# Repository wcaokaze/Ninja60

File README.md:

Ninja60 (WIP)
================================================================================

私の手にフィットするように設計した60%キーボードです

いわゆる左手デバイスとして使うことも想定しているのでロータリーエンコーダを4つ付ける予定です

ビルドガイド
--------------------------------------------------------------------------------

とくにカスタマイズなどしないのであれば[things](things)に出力済みのstlがあります

カスタマイズする場合は[scad](scad)をご覧ください

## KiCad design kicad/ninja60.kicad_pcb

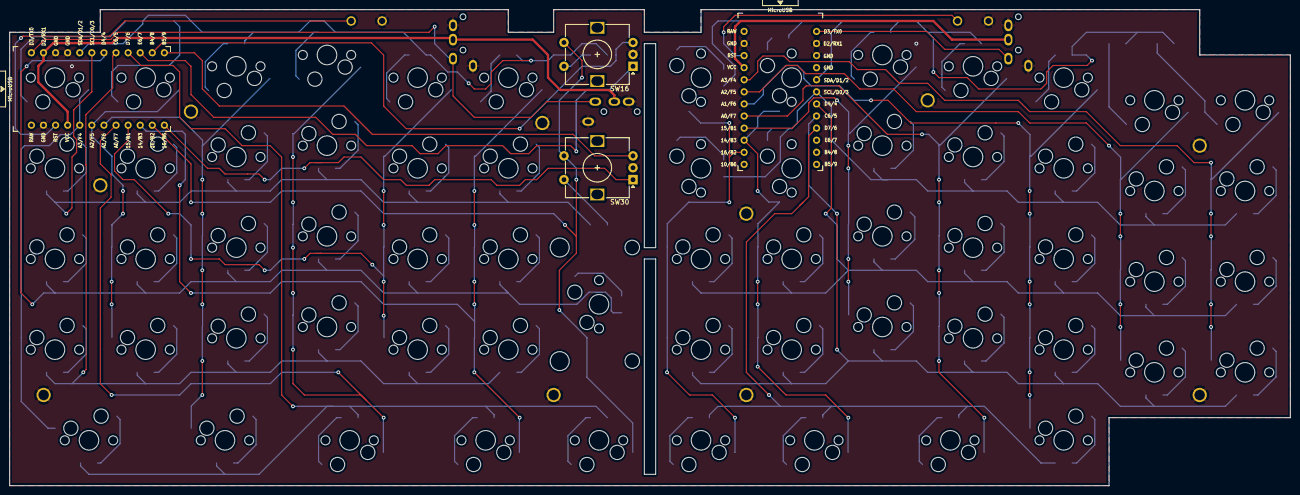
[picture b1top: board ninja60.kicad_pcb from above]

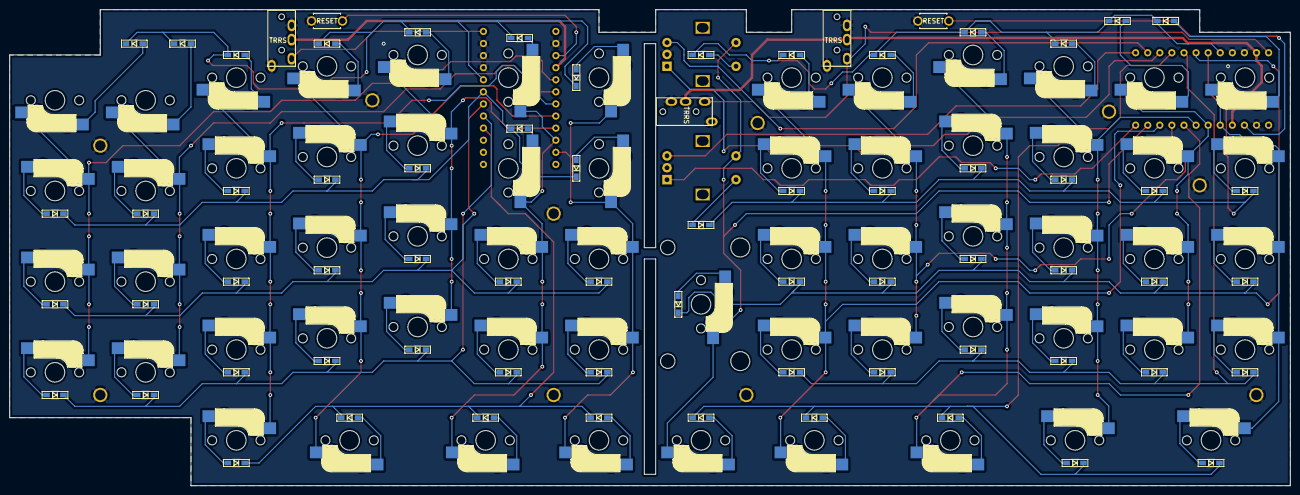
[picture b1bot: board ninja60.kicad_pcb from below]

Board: 2 copper layers, 269.1 x 100.0 mm, 136 parts (69 on the bottom side), 99 nets.

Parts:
D1, D2, D3, D4, D5, D6, D7, D8, D9, D10, D11, D12, D13, D14, D15, D16, D17, D18, D19, D20, D21, D22, D23, D24, D25, D26, D27, D28, D29, D30, D31, D32, D33, D34, D35, D36, D37, D38, D39, D40, D41, D42, D43, D44, D45, D46, D47, D48, D49, D50, D51, D52, D53, D54, D55, D56, D57, D58, D59, D60, D61, D62, D63, D64: D; D3_SMD_v2
J1, J2, J3: MJ-4PP-9; MJ-4PP-9_1side
Ref**: Val**; CherryMX_MidHeight_Choc_Hotswap_2U_Outline
SW1, SW2: SW_PUSH; ResetSW_1side
SW3, SW4, SW5, SW6, SW7, SW8, SW9, SW10, SW11, SW12, SW13, SW14, SW15, SW17, SW18, SW19, SW20, SW21, SW22, SW23, SW24, SW25, SW26, SW27, SW28, SW29, SW31, SW32, SW33, SW34, SW35, SW36, SW37, SW38, SW39, SW40, SW41, SW42, SW43, SW44, SW45, SW46, SW47, SW48, SW49, SW50, SW51, SW52, SW53, SW54, SW55, SW56, SW57, SW58, SW59, SW62, SW63, SW66: SW_PUSH; CherryMX_Hotswap
SW16, SW30: Rotary_Encoder_Switch; RotaryEncoder_Alps_EC12E-Switch_Vertical_H20mm
SW60, SW61, SW64, SW65: SW_PUSH; CherryMX_Hotswap_1.5u
U1, U2: ProMicro; ProMicro_v3.5

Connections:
GND: J1.A, J1.B, J2.A, J2.B, J3.A, J3.B, SW1.2, SW2.2, SW16.C, SW30.C, U1.3, U1.4, U1.23, U2.2, U2.3, U2.4, U2.23
unnamed: D1.2, SW3.2
unnamed: D2.2, SW4.2
unnamed: D3.2, SW5.2
unnamed: D4.2, SW6.2
unnamed: D5.2, SW7.2
unnamed: D6.2, SW8.2
unnamed: D7.2, SW9.2
unnamed: D8.2, SW10.2
unnamed: D9.2, SW11.2
unnamed: D10.2, SW12.2
unnamed: D11.2, SW13.2
unnamed: D12.2, SW14.2
unnamed: D13.2, SW15.2
unnamed: D14.2, SW16.S1
unnamed: D15.2, SW17.2
unnamed: D16.2, SW18.2
unnamed: D17.2, SW19.2
unnamed: D18.2, SW20.2
unnamed: D19.2, SW21.2
unnamed: D20.2, SW22.2
unnamed: D21.2, SW23.2
unnamed: D22.2, SW24.2
unnamed: D23.2, SW25.2
unnamed: D24.2, SW26.2
unnamed: D25.2, SW27.2
unnamed: D26.2, SW28.2
unnamed: D27.2, SW29.2
unnamed: D28.2, SW30.S1
unnamed: D29.2, SW31.2
unnamed: D30.2, SW32.2
unnamed: D31.2, SW33.2
unnamed: D32.2, SW34.2
unnamed: D33.2, SW35.2
unnamed: D34.2, SW36.2
unnamed: D35.2, SW37.2
unnamed: D36.2, SW38.2
unnamed: D37.2, SW39.2
unnamed: D38.2, SW40.2
unnamed: D39.2, SW41.2
unnamed: D40.2, SW42.2
unnamed: D41.2, SW43.2
unnamed: D42.2, SW44.2
unnamed: D43.2, SW45.2
unnamed: D44.2, SW46.2
unnamed: D45.2, SW47.2
unnamed: D46.2, SW48.2
unnamed: D47.2, SW49.2
unnamed: D48.2, SW50.2
unnamed: D49.2, SW51.2
unnamed: D50.2, SW52.2
unnamed: D51.2, SW53.2
unnamed: D52.2, SW54.2
unnamed: D53.2, SW55.2
unnamed: D54.2, SW56.2
unnamed: D55.2, SW57.2
unnamed: D56.2, SW58.2
unnamed: D57.2, SW59.2
unnamed: D58.2, SW60.2
unnamed: D59.2, SW61.2
unnamed: D60.2, SW62.2
unnamed: D61.2, SW63.2
unnamed: D62.2, SW64.2
unnamed: D63.2, SW65.2
unnamed: D64.2, SW66.2
VCC: J1.C, J3.C, U1.2, U1.21
encoder0_a: SW16.A, U1.10
encoder0_b: SW16.B, U1.11
encoder1_a: SW30.A, U1.13
encoder1_b: SW30.B, U1.12
l_col0: SW3.1, SW17.1, SW31.1, SW45.1, SW58.1, U1.20
l_col1: SW4.1, SW18.1, SW32.1, SW46.1, U1.19
l_col2: SW5.1, SW19.1, SW33.1, SW47.1, SW59.1, U1.18
l_col3: SW6.1, SW20.1, SW34.1, SW48.1, SW60.1, U1.17
l_col4: SW7.1, SW21.1, SW35.1, SW49.1, U1.16
l_col5: SW8.1, SW22.1, SW36.1, SW50.1, SW61.1, U1.15
l_col6: SW16.S2, SW30.S2, SW37.1, SW62.1, U1.14
l_data: J1.D, J3.D, U1.1
l_reset: SW1.1, U1.22
l_row0: D1.1, D2.1, D3.1, D4.1, D5.1, D6.1, D14.1, U1.5
l_row1: D15.1, D16.1, D17.1, D18.1, D19.1, D20.1, D28.1, U1.6
l_row2: D29.1, D30.1, D31.1, D32.1, D33.1, D34.1, D35.1, U1.7
l_row3: D43.1, D44.1, D45.1, D46.1, D47.1, D48.1, U1.8
l_row4: D56.1, D57.1, D58.1, D59.1, D60.1, U1.9
r_VCC: J2.C, U2.21
r_col0: SW15.1, SW29.1, SW44.1, SW57.1, U2.20
r_col1: SW14.1, SW28.1, SW43.1, SW56.1, U2.19
r_col2: SW13.1, SW27.1, SW42.1, SW55.1, SW66.1, U2.18
r_col3: SW12.1, SW26.1, SW41.1, SW54.1, SW65.1, U2.17
r_col4: SW11.1, SW25.1, SW40.1, SW53.1, U2.16
r_col5: SW10.1, SW24.1, SW39.1, SW52.1, SW64.1, U2.15
r_col6: SW9.1, SW23.1, SW38.1, SW51.1, SW63.1, U2.14
r_data: J2.D, U2.1
r_reset: SW2.1, U2.22
r_row0: D7.1, D8.1, D9.1, D10.1, D11.1, D12.1, D13.1, U2.5
r_row1: D21.1, D22.1, D23.1, D24.1, D25.1, D26.1, D27.1, U2.6
r_row2: D36.1, D37.1, D38.1, D39.1, D40.1, D41.1, D42.1, U2.7
r_row3: D49.1, D50.1, D51.1, D52.1, D53.1, D54.1, D55.1, U2.8
r_row4: D61.1, D62.1, D63.1, D64.1, U2.9

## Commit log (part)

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2020-11-13 試作2号のデータをコピー
2020-12-17 とりあえず台形のみ作成
2020-12-17 角を丸くした
2020-12-18 テント/チルト型にしてみた
2020-12-18 四角錐といいますか、上の方が狭い形にしてみました
2020-12-18 ステム部を作りました
2020-12-18 ステムの周りに柱を立てます
2020-12-18 ステム周りにさらに円柱立てていく
2020-12-18 向きがわかるようにわずかに柱の高さを変えた
2020-12-18 1U以外のサイズのキーキャップも作れるようにしました。1.75Uしか使わないですけどね
2020-12-19 シリンドリカルのキーも多少斜めっているかのように見えるようにした
2020-12-19 縦長のキーも作れるようにした
2020-12-19 ステムの周りの柱を0.5mm下げた
2020-12-19 ステム以外を全体的に上に上げた
2020-12-20 ステムが一番奥まで入らない説があったのでさらに1mm高くしました
2020-12-20 ホームポジションのマークをつけた
    ホームポジションのマークってなんか名前あった気がするけど思い出せないのでhome_position_markにしてます
2020-12-20 ホームポジションマークの位置と大きさを調整
2020-12-20 背の高いfnキーを7列目に移動
2020-12-20 右手側が山の形になるように並び替え
2020-12-20 キー同士の距離が1mmもない状態だったので広くしました
2020-12-20 左手側最下段のキーを右手側最下段と重なる位置に移動
2020-12-21 あと2キー出力できる空間がありそうなので左手7列目を2つ追加
2020-12-22 キーが多すぎてレンダリングできなかったので半分だけ出力します
2020-12-22 上二段を下二段の上に重ねます
2020-12-22 7列目縦長キーの上にホームポジションキーを重ねます
2020-12-22 残りのキーをうまく重ねます
2020-12-23 キーキャップmoduleを別ファイルに移動
2020-12-25 すべてのキーをバラバラに出力してから統合する手法に移行
2020-12-25 ボトムプレートのソケットとかダイオード用の穴をまず作ります
2020-12-26 試しに4キー分だけ作ってみた
2020-12-26 穴開ける用のキースイッチの形状を作成
2020-12-26 トッププレート4キー分作成
2020-12-27 予め回転、移動させた状態でstlを出力するようにした
2020-12-30 refactored: moduleの定義順変更
2020-12-30 ステム部、outerではなくinnerでくり抜くように変更
2020-12-30 ステム部などの円柱を16角柱で代用
2020-12-30 行方向の丸みを強くした
2021-01-03 一旦調整するのでキーキャップ2個だけ並べます
2021-01-03 変数達を先に宣言した方が見やすいきがしました
2021-01-03 中の空洞やっぱり球状に戻します 分厚すぎなので
2021-01-03 ステム部の高さが全然足りてないししかも中心からズレていたのを修正
2021-01-03 ステム部が別になったので他の部分をすべてステム部の高さ分下げます
2021-01-03 柱さらに0.5mm低くします
2021-01-03 クソ縦長キーキャップをやめたことによりもう少し各キー同士の間隔を詰められるようになったので詰めます
2021-01-03 柱の形状を再調整
2021-01-04 ステム部とキーキャップをジョイントするための十字を作成
2021-01-04 高さ足りてなかったのでちゃんと低い方の端の高さを計算するようにしました
2021-01-04 y = [0, 1] => [0.5, 1.5]
2021-01-04 長いキーに傾きをつけました
2021-01-04 refactored: keycap_with_stem追加
2021-01-04 壁があるときは柱を壁まで延ばすようにしました
2021-01-05 キーキャップの外形を刷新、南から北に向かって高くなっていく形状にした
2021-01-05 added: part_cylinder
2021-01-05 そんなことしなくても一時的に$faを変える方法があったらしい もっと早く教えろ
2021-01-06 x < -3 のときの柱を十字に変更
2021-01-06 ケースの曲面用のfaを分けます
2021-01-06 曲面を再度調整
2021-01-06 キーキャップ間の隙間を詰めました
2021-01-06 柱を繰り抜く際outerではなくinnerを使用 わずかに処理が速いので
2021-01-06 いつまでwalls残してんねんコイツ
2021-01-06 本番用visible_faをコメントアウト
2021-01-06 柱を繰り抜く際innerではなくouterを使用するように戻した childrenが反映されなくなってたので
2021-01-06 縦長キーの座標間違えてたので修正
2021-01-07 各moduleにコメントを書いておきました
2021-01-07 renamed: visible_fa => keycap_visible_fa, invisible_fa => keycap_invisible_fa, thickness => keycap_thickness
2021-01-07 renamed: height => keycap_height
2021-01-07 各パーツごとにファイルを分けました
2021-01-07 結合部の寸法の微調整が簡単にできるようにしました
2021-01-07 ステムホルダー タテヨコがパッとわかるようにしたかったので横長にしました
2021-01-07 キーキャップの時と同様に各パーツごとに$faをべつべつに指定
2021-01-08 親指のキーたちを円弧状に配置する試み
    結局こうなる
    先人たちに逆らおうとしたってそうはいかない
2021-01-09 各列1°ずつ開いて並べることにします
2021-01-10 角度、座標など微妙にズレがあったので修正
2021-01-10 refactored: keycap_marginという変数を定義しました
2021-01-10 y == -1のキーが実際には下から2段目なのでこのズレを考慮した処理に変更
2021-01-10 各列の角度を2.5°に変更
2021-01-10 staggeredによってy = 1.25とかに配置されるキーも上面の角度はy = 1として出力
2021-01-10 南北の凹みを繋げられるようにした
2021-01-11 親指キーの皿部分を作成
2021-01-16 親指キーの空洞を開けた
2021-01-17 親指キーの柱部分作成
2021-01-18 静音リング部を別パーツに分けた
2021-01-24 刻印を追加
2021-02-01 人差し指で押すつもりだった3キーを小指側に移動
2021-02-01 staggered単位をmmに変更
2021-02-01 いつまで最下段キーのコメントアウト残してんねんこんなもんもう絶対使わんやろ
2021-02-01 親指キーの大きさと位置再調整
2021-02-01 小指外側のキーの柱を十字型に変更
2021-02-03 ケースを2Uずらしたときにbottom_zの計算式を2Uずらすの忘れていたので修正
2021-02-03 親指キーに渡す引数を間違えてクソデカステムが生成されていたのを修正
2021-02-06 小指キー一列減らして親指1キー増やした
2021-02-06 ロータリーエンコーダを配置
2021-02-20 親指キーの側面がポリゴンみたいになってたを曲線に修正、皿部分が扇型だったのを普通のキーキャップと同様長方形に変更
2021-02-22 横キーピッチを18mmに変更、縦は16mmのまま
2021-02-23 皿部分の面積がすべてのキーでほぼ同じになるように調整
2021-02-25 SAプロファイルっぽく底面をシャープに、上面は丸くした
2021-02-25 faをより細かく場所ごとに設定できるようにした
    したけどどっちみち全部2になりそうだった
2021-02-26 親指用キーキャップの引数を中心ではなく外側の半径に変更
2021-02-26 ちょっと皿広くした
2021-02-26 小指と人差し指の外側キーまでの距離だけを16mmに変更
2021-03-01 moved: { 試作3号 => _ }/kicad, { 試作3号 => _ }/scad
2021-03-01 moved: { scad => _ }/res/Cica-Regular.ttf
2021-03-20 GradleからOpenSCAD叩かせます
2021-03-21 使いそうなものをscadwriterとして用意しました
2021-03-21 *.scadの生成と*.stlの生成は違うタスクにしないとさ、うまくいかないよね
2021-03-21 ビルド方法のメモを残しておきました
2021-03-21 added: $fs, $fa, $fn
2021-03-21 cylinderの引数名を明示
2021-03-21 linearExtrude => linear_extrude
2021-03-21 added: <Double>..<Double> step <Double> (Iterable<Double>)
2021-03-21 moved: scadwriter.{ _ => foundation }.Point3d
2021-03-21 added: Angle, Size
2021-03-21 SizeとAngleに各種演算子オーバーロードを実装
2021-03-22 moved: *.scad => com/wcaokaze/ninja60/scadgenerator/*.kt
2021-03-26 foostan/kbdをサブモジュールに追加、kicadにシンボルライブラリを通しました
2021-05-18 openscadのインストール用コマンドのメモを多少親切にした
2021-05-29 moved: com.wcaokaze.ninja60.{ scadgenerator => _ }.*, com.wcaokaze.{ ninja60.scadgenerator.scadwriter => _ }.*
2021-06-02 added: Column
2021-06-02 Columnの各KeyPlateのレイヤー位置をずらせるようにした
2021-06-06 keycapThicknessをKeycapのcompanion objectに移動
2021-06-06 renamed: keyswitch.kt => muteForm.kt
2021-06-06 renamed: topPlate => TopPlate
2021-06-06 added: AlphanumericColumns
2021-06-07 見やすくするためレイヤーを一層だけにした
2021-06-07 scad書き出し処理をTopPlate.ktに移動
2021-06-07 deleted: muteForm.kt
    ミュート使うのやめます
2021-06-07 deleted: KeyPlate.U
2021-06-08 4行6列固定になっていたのを可変に変更。無理そうなら戻します
2021-06-10 added: Vector2d, Vector3d
2021-06-10 added: Line2d, Line3d
2021-06-12 added: Point3d.rotate(Line3d, Angle): Point3d
2021-06-14 added: Line3d.translate, rotate, Vector3d.rotate
2021-06-14 deleted: rotateX, rotateY, rotateZ
2021-06-14 added: Plane3d.intersection(Line3d): Point3d
2021-06-16 added: Vector.innerProduct, vectorProduct, angleWith
2021-06-16 KeyPlateの内部構造を点4つから中心、大きさ、向きふたつに変更
2021-06-20 各プレート同士をつなげた
2021-06-25 一旦List<List<Point3d>>生成するのやめていきなりscad書きます
2021-06-27 KeyPlateの端の部分がきっちり垂直に生成されていなかったのを修正
2021-06-28 キースイッチはめる用の穴を開けました
2021-06-29 確認用にlayerDistance = 0mmのAlphanumericColumnsも表示
2021-06-29 1行目がキー半個分深い位置に生成されてしまっていたのを修正
2021-06-29 左右の一番外側の列を内側に近づけた
2021-06-29 『ひねり』を8°くらいまで落とさないとキー同士が干渉しすぎて無理だと思った
2021-06-29 『ひねり』とは別にColumnそのものを回転させるパラメータも追加
2021-07-12 左右の端に壁を作りました
2021-07-12 なんかもうベツモノになりすぎたので試作の写真を削除
    基板も刻印もなくなったので一旦謝辞も削除
    しかし感謝の心はあります
2021-07-27 refactor: added translate(Vector3d, Size)
2021-07-27 added: ThumbPlate
2021-07-31 作業中にlayerDistanceをいじっていた痕跡が残っていたのを修正
2021-07-31 親指キーの長さを変更できるようにした
    とりあえず1.5U
2021-07-31 親指キーの長さを22.4mmに変更
2021-08-04 数字行を垂直にしてたのを通常の向きに変更
    数字行は使用頻度は高くないものの連続して打たれやすいという性質があるため
    垂直に配置しているとすごく打ちづらいんですね
2021-08-04 左右の壁をなくした
2021-08-04 Revert "AlphanumericPlateを各キーごとに板で出力しようとした版の途中"
    This reverts commit ffdb721cf2262750bd326013f6ed69e2614445aa.
2021-08-05 AlphanumericPlateとThumbPlateを移動できるようにした
2021-08-05 deleted: case.kt
2021-08-09 KeyPlateとKeySwitchを別の概念として分けた。キースイッチの位置と向きだけを持つべき、大きさを持つべきでない部分はすべてKeySwitchに置換
2021-08-09 AlphanumericColumnsとAlphanumericPlate、ThumbKeysとThumbPlateを分ける意味がなくなったのでPlate側に統合
2021-08-10 各Columnの上下端を20mm延ばすようにした
    こうしないとColumn同士の境目の壁が垂直に出力されない
2021-08-11 renamed: Column => AlphanumericColumn
2021-08-11 renamed: alphanumericPlate => hullAlphanumericPlate, thumbPlate => hullThumbPlate
2021-08-14 alphanumericの手前部分ケース作成
2021-08-14 パームレスト部分をとりあえずcubeで置いた
2021-08-22 4段目キーの長さを1.5Uに変更
2021-08-28 KeySwitch.LayoutSizeが追加されたことでより正確に計算できるところがありますね
2021-08-29 added: Transformable
2021-08-29 RotaryEncoderMountHoleにTransformableを実装し忘れてたので実装しました
2021-08-29 ThumbPlateにもTransformableを実装し忘れてたので実装しました
2021-08-29 親指の奥のキーの位置が通常より遠くなっていたのを修正
2021-08-30 アルファベットキーの手前の壁 きちんと角度計算するようにした
2021-09-01 後ろの斜面部分がデコボコしててダサかったので平らにしました
2021-09-06 手前側ロータリーエンコーダの取り付け穴を作りました
2021-09-08 無駄な括弧を削除
2021-09-08 locale(Point3d) 追加
2021-09-10 他のモデル達と同じようにCaseもAlphanumericPlateとThumbPlateを保持するようにします
2021-09-10 Case以外一旦出力しないようにしておきます
2021-09-10 STLを追加
2021-09-10 右手側出力するの忘れてました。しました
2021-09-11 かんたんにREADMEを書きました
2021-09-12 added: Gear
2021-09-13 renamed: Gear.PRESSURE_ANGLE => PROFILE_ANGLE
2021-09-13 added: Gear distance Gear
2021-09-13 奥側ロータリーエンコーダのノブを作成
2021-09-13 BackRotaryEncoderKnobと同様にFrontRotaryEncoderKnobも追加
2021-09-15 奥側ロータリーエンコーダにつける歯車を作成
2021-09-20 奥側ロータリーエンコーダに取り付ける歯車を作成
2021-10-31 奥側ロータリーエンコーダ部分のケースを作成
2021-11-05 ノブがハマる部分の穴を作成
2021-11-10 奥側ノブを取り付けるためのシャフトの穴を開けました
2021-11-24 added: LeftOutRotaryEncoderKnob
2021-11-25 LeftOutRotaryEncoderKnob内にInternalGearをいれました
2021-11-25 renamed: DoubelRangeIterator.kt => DoubleRangeIterator.kt
2021-11-27 added: LeftInnerRotaryEncoderKnob
2021-11-27 LeftInnerRotaryEncoderKnobを押し込むための穴をLeftOuterRotaryEncoderKnobに開けました
2021-11-27 手前側ロータリーエンコーダのノブ周りの穴を左側に合わせて狭くしました
2021-11-28 LeftOuterRotaryEncoderKnobの向き、AlphanumericPlateの左端を基準にした
2021-12-02 faの型をAngleに変更
2021-12-02 fsの型をSizeに変更
2021-12-20 後ろ側ロータリーエンコーダのノブにも滑り止めをつけました
2021-12-20 奥側ロータリーエンコーダのノブの滑り止めを1:1凸凹に変更
2021-12-20 added: rotaryEncoderKnobHole
2021-12-21 親指キーの表面を出力
2021-12-29 親指キーの配置再調整
2022-01-06 手前側ロータリーエンコーダのマウント穴の向きを調整
2022-01-11 CaseをTransformableに変更
2022-01-12 Size, AngleなどでtoStringがScadコード生成用のフォーマットになっていたのを修正、ScadPrimitiveValueを追加
2022-01-17 ScadObjectはScadValueを継承するようにした
2022-01-17 deleted: ScadWriter
2022-01-18 deleted: ScadValue.writeScad
2022-01-20 case生成処理をがっつり書き直しました
2022-02-23 中がよく見えるように一旦ケース外側の壁を消しました
2022-02-26 親指キーの配置を変更
    なんどめだナウシカ
    他のキーと干渉しない配置がもはやこれしかない
    あとついでにSize.div(Size): Double追加しました、角度の場合はAngle(length / radius)で
2022-02-26 手前側ロータリーエンコーダの横のキーを追加
2022-03-01 added: place(Transformable) { children... }
2022-03-01 switchHoleとswitchSideHolderをmemoizeできるようにした
2022-03-12 added: Transformable.btLine, lrLine, fbLine
2022-03-12 added: Point distance Point
2022-03-27 added: BevelGear
2022-03-30 奥側ロータリエンコーダの位置を調整
2022-03-30 各種Rangeにおいてstartがendよりデカいときにstepを負値にしないといけなかったのを修正
2022-04-01 BackRotaryEncoderMediationGearの位置決めの計算に「Z座標」を使っており回転した場合に正確に位置が決まらなくなっていたのを修正
2022-04-03 歯車のサイズなど微調整
2022-04-06 PropagatedValue.valueはScadParentObjectじゃなくてScadObjectに定義しとかないとtoScadRepresentation内で使えないということに気づきました
2022-04-08 faをPropagatedValueに変更
2022-04-08 fsをPropagatedValueに変更
2022-04-08 provideValueの子が全く出力できていなかったのを修正
2022-04-08 先程の変更によってTopLevelScadObjectが無駄な{}を生成してたのも修正できるようになったのでついでに修正しときます
2022-04-08 writeScad直下にすべてのPropagatedValueを明示
2022-04-08 deleted: $fn
2022-04-15 alphanumeric手前側壁を作成
2022-04-16 手前の壁、ノブより左側と右側で分けてそれぞれ最適な高さとかにした
2022-04-17 FrontRotaryEncoder関係のコードからマジックナンバーを排除
2022-04-17 扇形のoffsetをきっちり並行に生成するようにした
2022-04-18 FrontRotaryEncoderKey部分のケースを作成
2022-04-19 親指周りの位置とかデカさとか諸々調整
2022-04-20 added: KeySwitch.KEYCAP_SURFACE_HEIGHT
2022-04-20 親指キーのキーピッチをキーの中心で計算してたけど扇形の内側で計算しないとキー同士がぶつかりますよね
2022-04-20 バウムクーヘン型を生成する関数を作った
2022-04-20 switchHoleにて上部に0.5mm余裕に穴を開けてるつもりが開いてなかったのを修正
2022-04-23 全体的に低くしたった
2022-04-23 パームレスト追加
2022-04-24 モジュールちゃんと分けましょうよってことですね
2022-04-24 shared.ktにあった関数とかをそれぞれのファイルに分けた
2022-04-24 Case.kt内にあるSCAD生成関数をパーツごとにファイルに分割
2022-04-24 Case(data class)とscad生成用関数のパッケージを分けた
2022-04-24 各パーツのインスタンス化の方法、companion objectのinvokeだったのをすべてCaseが担当するようにした
    それに伴いケース上での配置に関係する情報はcaseのモジュールに移動
2022-04-25 renamed: thumbPlateCase => thumbPlateHole
2022-04-27 added: thumbKeyCase
2022-04-27 thumbKeyCaseの引数でPlaneを受け取らないようにした
2022-05-02 thumbKeyCase呼び出すときにminWallThicknessつけてるのに関数内部でさらにminWallThickness足してたのを修正
2022-05-02 thumbHomeKeyの壁の厚みが0で生成されてたのを修正
2022-05-03 thumbHomeKeyの手前の壁をthumbPlateの壁となめらかに繋がるようにした
2022-05-04 ザッと見て適当に高速化できそうなとこはした
2022-05-04 親指部分にFrontRotaryEncoderの円筒が食い込んでいたのを修正
2022-05-04 thumbHomeKeyとthumbPlateがつながるようにした
2022-05-04 alphanumericとfrontRotaryEncoderKeyがつながるようにした
2022-05-05 wristRestを生成するかどうかをプログラム引数で決めれるようにした
2022-05-05 古いbackRotaryEncoderCaseはもはや約に立たないためごっそり削除
2022-05-11 backRotaryEncoderの歯車を取り付ける部分の左側だけを作った
2022-05-12 backRotaryEncoderKnobを取り付ける柱を支える壁をつけた
2022-05-14 backRotaryEncoderGearHolderLeftArmの上が削れてしまっていたのを修正
2022-05-14 backRotaryEncoderCaseに開ける穴をロータリーエンコーダの大きさにした
2022-05-14 BackRotaryEncoderGearのサイズとかPrinterAdjustmentsに基づくようにした
2022-05-15 added: backRotaryEncoderGearHolderRightArm
2022-05-15 backRotaryEncoderGearHolderRightArmと右の列の間にできてた隙間を埋めました
2022-05-16 ローカルclassだったBackRotaryEncoderGearHolderLeftArmをpublicなところに移動
2022-05-17 ローカルclassだったBackRotaryEncoderGearHolderRightArmをpublicなところに移動
2022-05-21 BackRotaryEncoderGearHolderLeftArmとノブの間に隙間を作った
2022-05-21 ちょっとコードを綺麗にした気がする
2022-05-21 BackRotaryEncoderGearHolderRightArmにもでっぱりを作った
2022-05-22 Placeableをscadutilに移動
2022-05-22 added: Location, locate
2022-05-22 deleted: locale
2022-05-22 MediationGear部分にもでっぱりを作成
2022-05-23 Location, Transformable, Placeableをscadwriterに移動
2022-05-25 Point3dにTransformableを実装
2022-05-25 Line3dにTransformableを実装
2022-05-25 Transformableからtranslate(Size3d)を削除
    これはもともとscadwriterのモジュールにVector3dがなく
    仕方なくtranslate(Size3d)としていたなごりであり、
    本来移動距離を表すのにSize3dよりVector3dのほうが向いているのは言うまでもない
2022-05-25 Vector2d, Vector3dをScadValueにした
